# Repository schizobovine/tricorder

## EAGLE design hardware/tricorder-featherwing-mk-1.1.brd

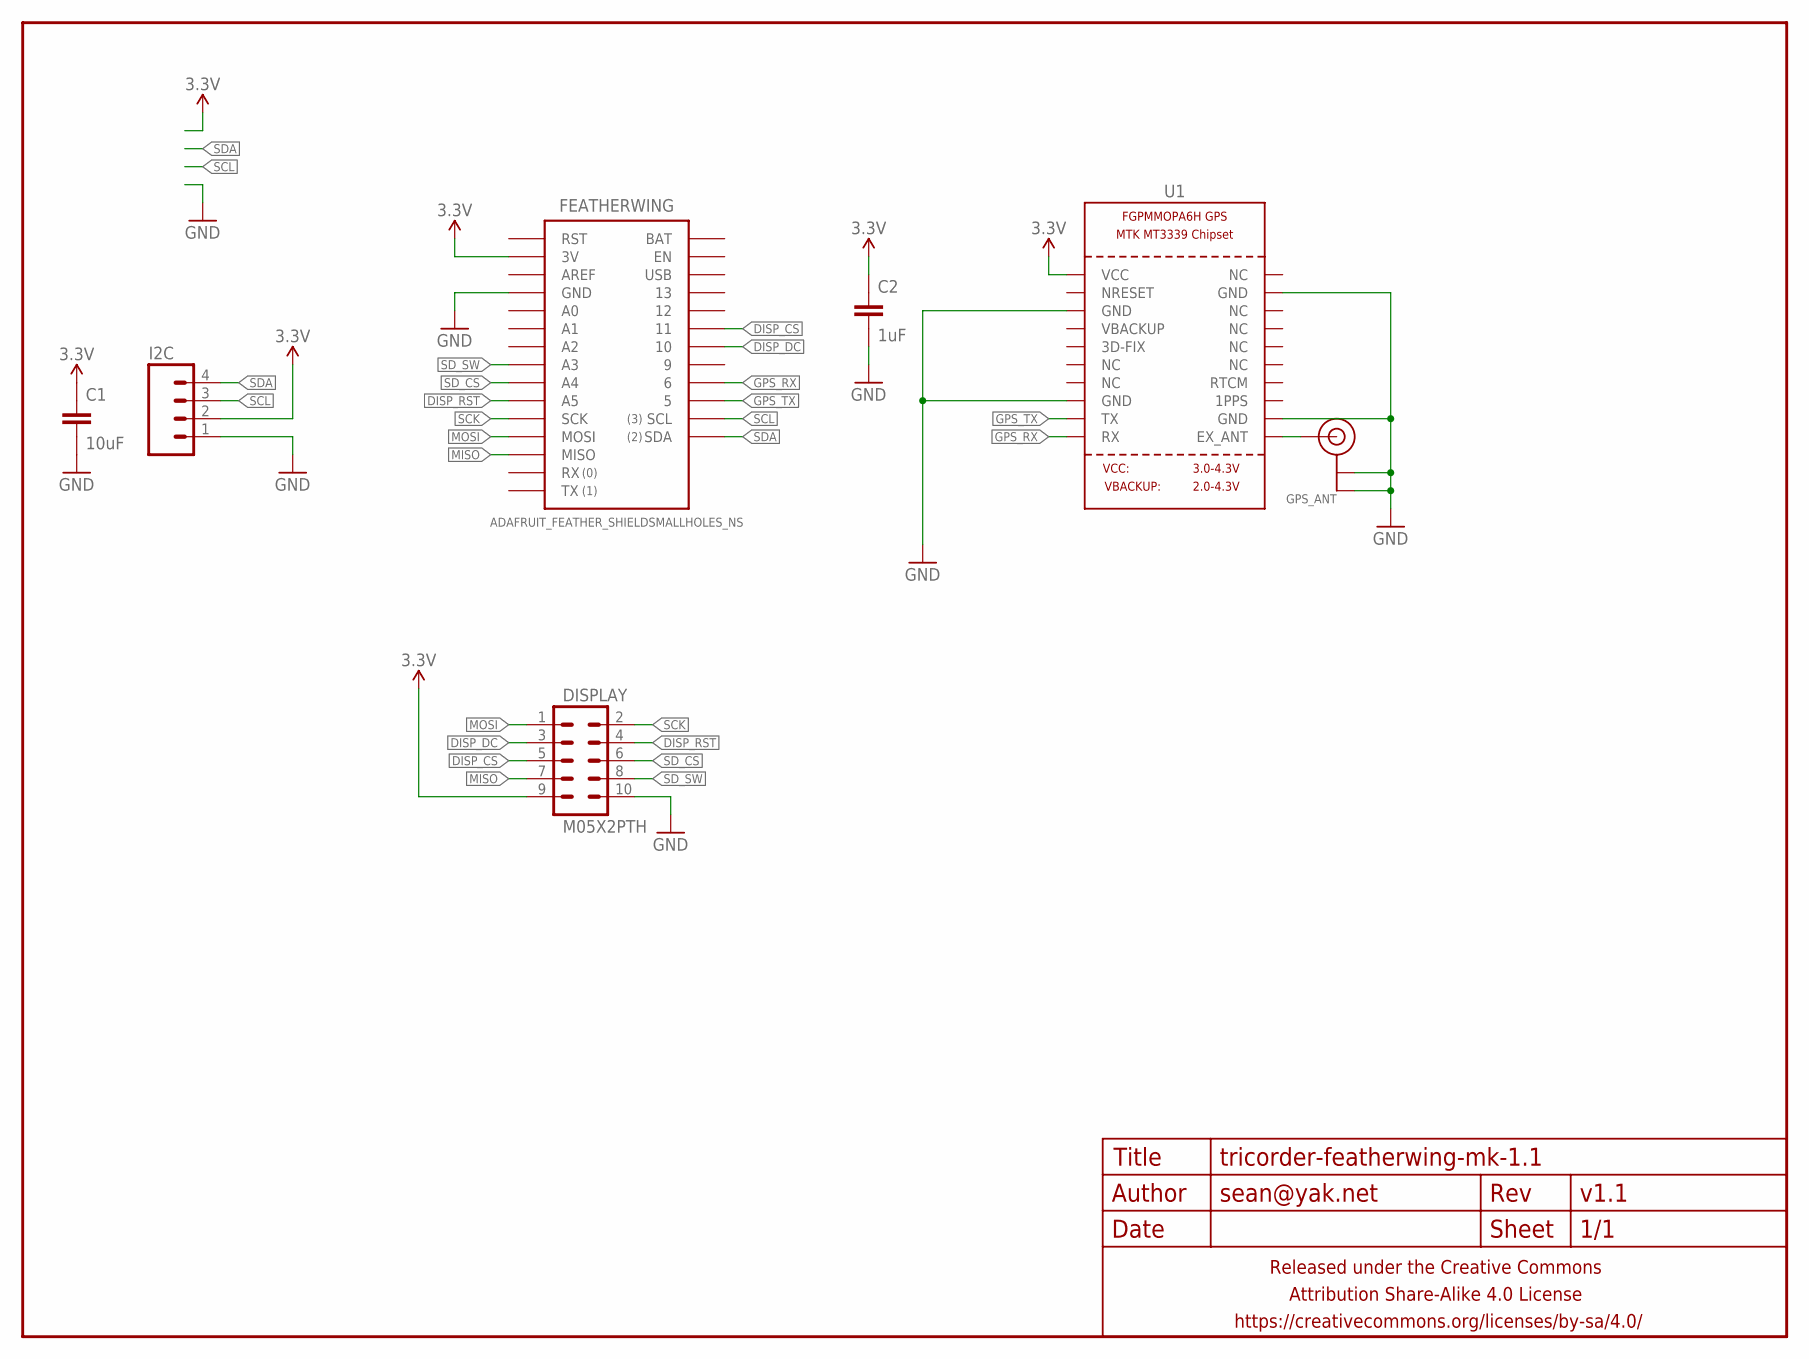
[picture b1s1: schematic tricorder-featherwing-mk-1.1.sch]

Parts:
C1: 10uF; C1210
C2: 1uF; C0603
DISPLAY: M05X2PTH; AVR_ICSP
FEATHERWING: ADAFRUIT_FEATHER_SHIELDSMALLHOLES_NS; ADAFRUIT_FEATHER_SMALLHOLES_NS
FRAME1: FRAME-LETTERNO_PACKAGE; DUMMY
GPS_ANT: ANTENNA_U.FL; U.FL
I2C: M04PTH; 1X04-PTH-VERT
U1: GPS_FGPMMOPA6H; FGPMMOPA6H

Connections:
3.3V: C1.1, C2.1, DISPLAY.9, FEATHERWING.3V, I2C.2, U1.P$1 (VCC)
DISP_CS: DISPLAY.5, FEATHERWING.11
DISP_DC: DISPLAY.3, FEATHERWING.10
DISP_RST: DISPLAY.4, FEATHERWING.A5
GND: C1.2, C2.2, DISPLAY.10, FEATHERWING.GND@0 (GND), FEATHERWING.GND@1 (GND), GPS_ANT.1 (GND), GPS_ANT.2 (GND), I2C.1, U1.P$3 (GND), U1.P$8 (GND), U1.P$12 (GND), U1.P$19 (GND)
GPS_RX: FEATHERWING.6, U1.P$10 (RX)
GPS_TX: FEATHERWING.5, U1.P$9 (TX)
MISO: DISPLAY.7, FEATHERWING.MISO
MOSI: DISPLAY.1, FEATHERWING.MOSI
unnamed: GPS_ANT.3 (SIGNAL), U1.P$11 (EX_ANT)
SCK: DISPLAY.2, FEATHERWING.SCK
SCL: FEATHERWING.SCL, I2C.3
SDA: FEATHERWING.SDA, I2C.4
SD_CS: DISPLAY.6, FEATHERWING.A4
SD_SW: DISPLAY.8, FEATHERWING.A3

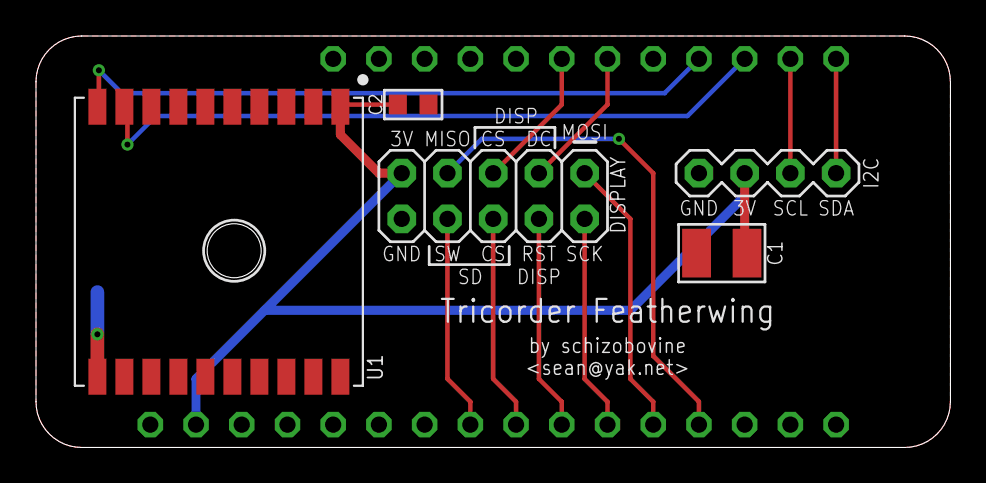
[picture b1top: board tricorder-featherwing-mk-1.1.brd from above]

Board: 2 copper layers, 50.8 x 22.9 mm, 8 parts (1 on the bottom side), 15 nets.

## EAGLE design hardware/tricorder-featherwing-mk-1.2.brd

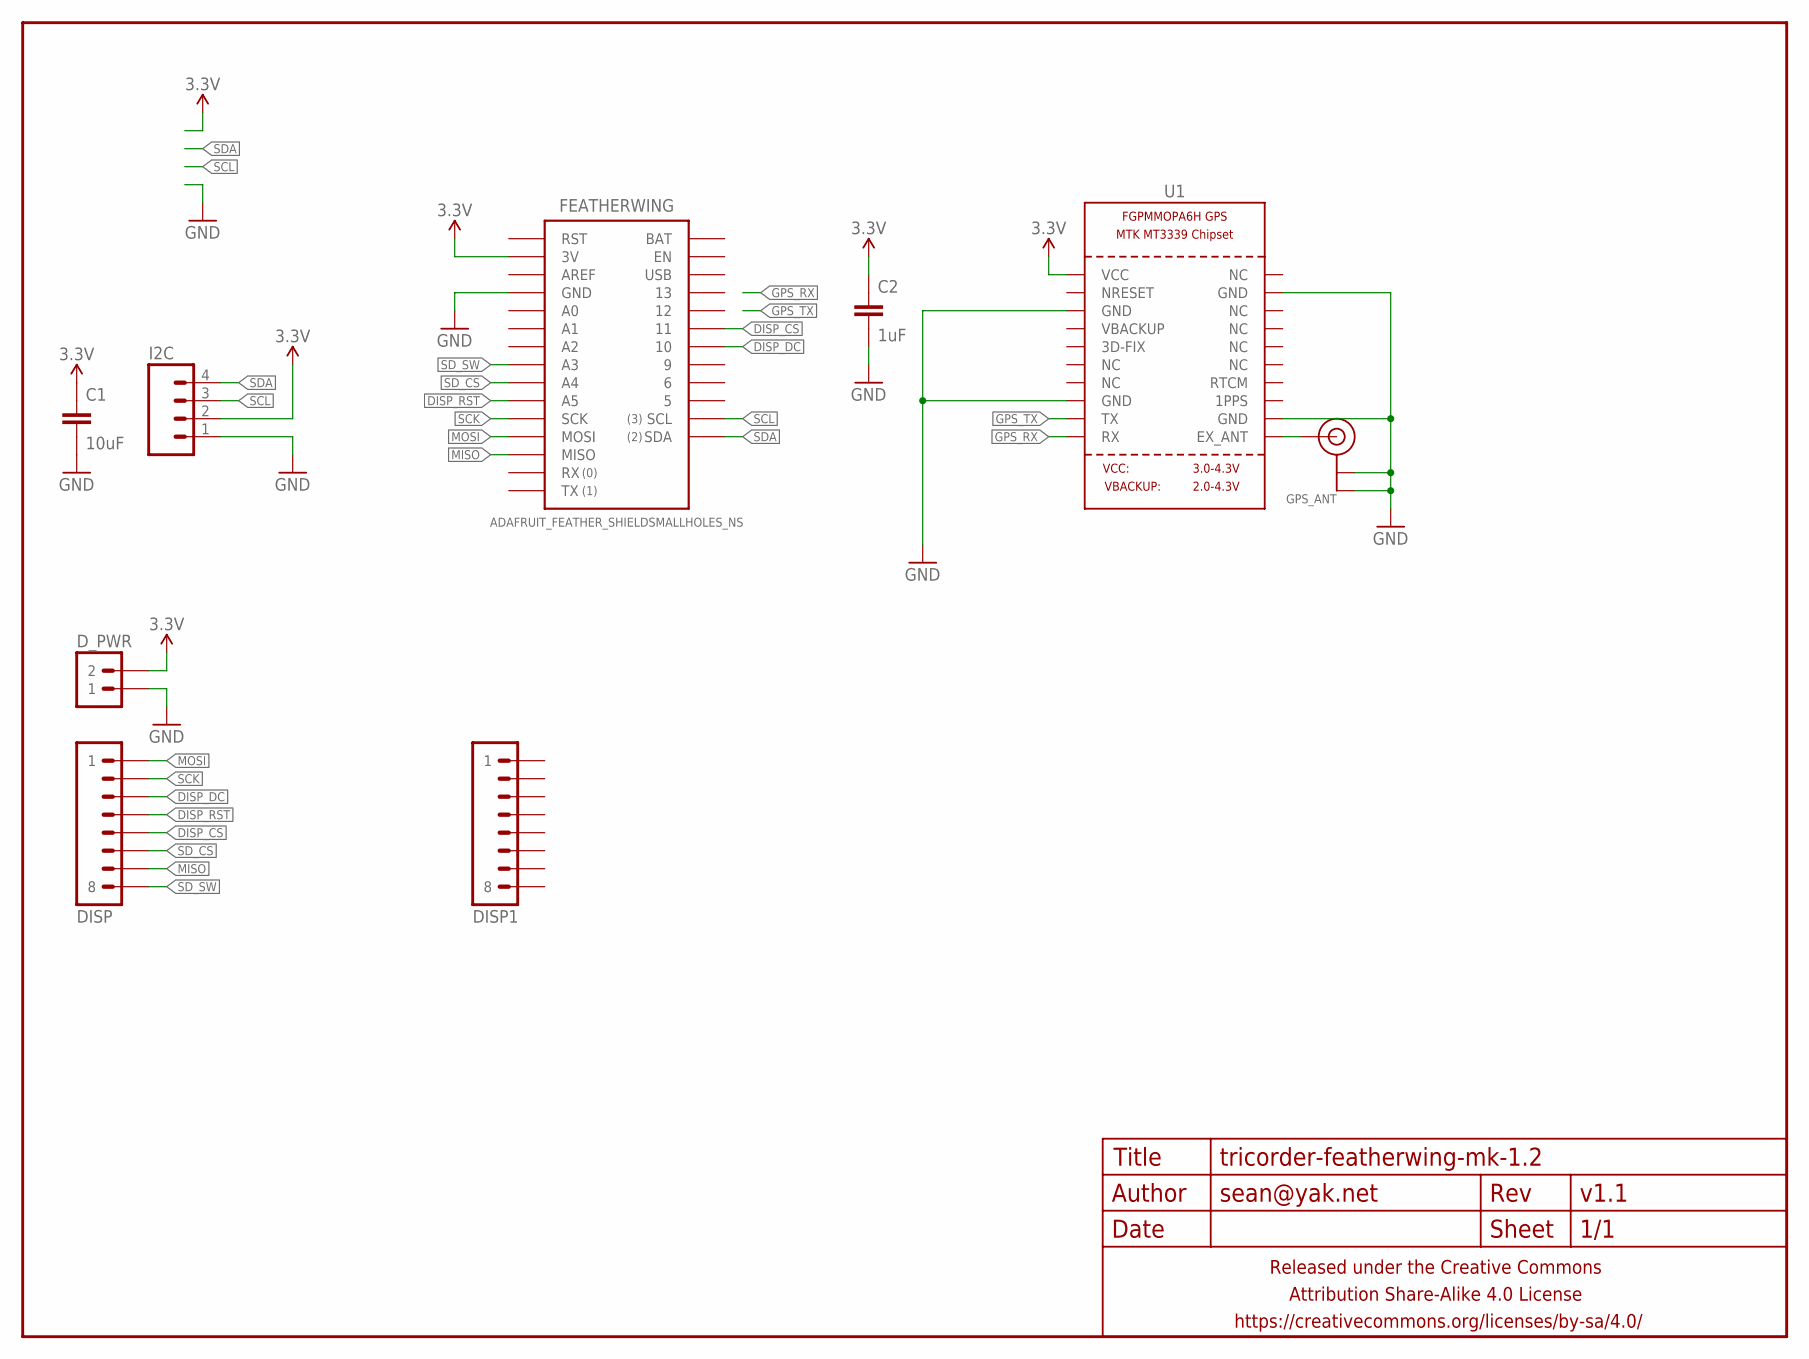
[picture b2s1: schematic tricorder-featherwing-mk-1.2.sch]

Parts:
C1: 10uF; C1210
C2: 1uF; C0603
DISP, DISP1: M081X08; 1X08
D_PWR: M02PTH; 1X02
FEATHERWING: ADAFRUIT_FEATHER_SHIELDSMALLHOLES_NS; ADAFRUIT_FEATHER_SMALLHOLES_NS
FRAME1: FRAME-LETTERNO_PACKAGE; DUMMY
GPS_ANT: ANTENNA_U.FL; U.FL
I2C: M04PTH; 1X04-PTH-VERT
U1: GPS_FGPMMOPA6H; FGPMMOPA6H

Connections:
3.3V: C1.1, C2.1, D_PWR.2, FEATHERWING.3V, I2C.2, U1.P$1 (VCC)
DISP_CS: DISP.5, FEATHERWING.11
DISP_DC: DISP.3, FEATHERWING.10
DISP_RST: DISP.4, FEATHERWING.A5
GND: C1.2, C2.2, D_PWR.1, FEATHERWING.GND@0 (GND), FEATHERWING.GND@1 (GND), GPS_ANT.1 (GND), GPS_ANT.2 (GND), I2C.1, U1.P$3 (GND), U1.P$8 (GND), U1.P$12 (GND), U1.P$19 (GND)
GPS_RX: U1.P$10 (RX)
GPS_TX: U1.P$9 (TX)
MISO: DISP.7, FEATHERWING.MISO
MOSI: DISP.1, FEATHERWING.MOSI
unnamed: GPS_ANT.3 (SIGNAL), U1.P$11 (EX_ANT)
SCK: DISP.2, FEATHERWING.SCK
SCL: FEATHERWING.SCL, I2C.3
SDA: FEATHERWING.SDA, I2C.4
SD_CS: DISP.6, FEATHERWING.A4
SD_SW: DISP.8, FEATHERWING.A3

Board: 2 copper layers, 10 parts (1 on the bottom side), 13 nets, no tracks yet.

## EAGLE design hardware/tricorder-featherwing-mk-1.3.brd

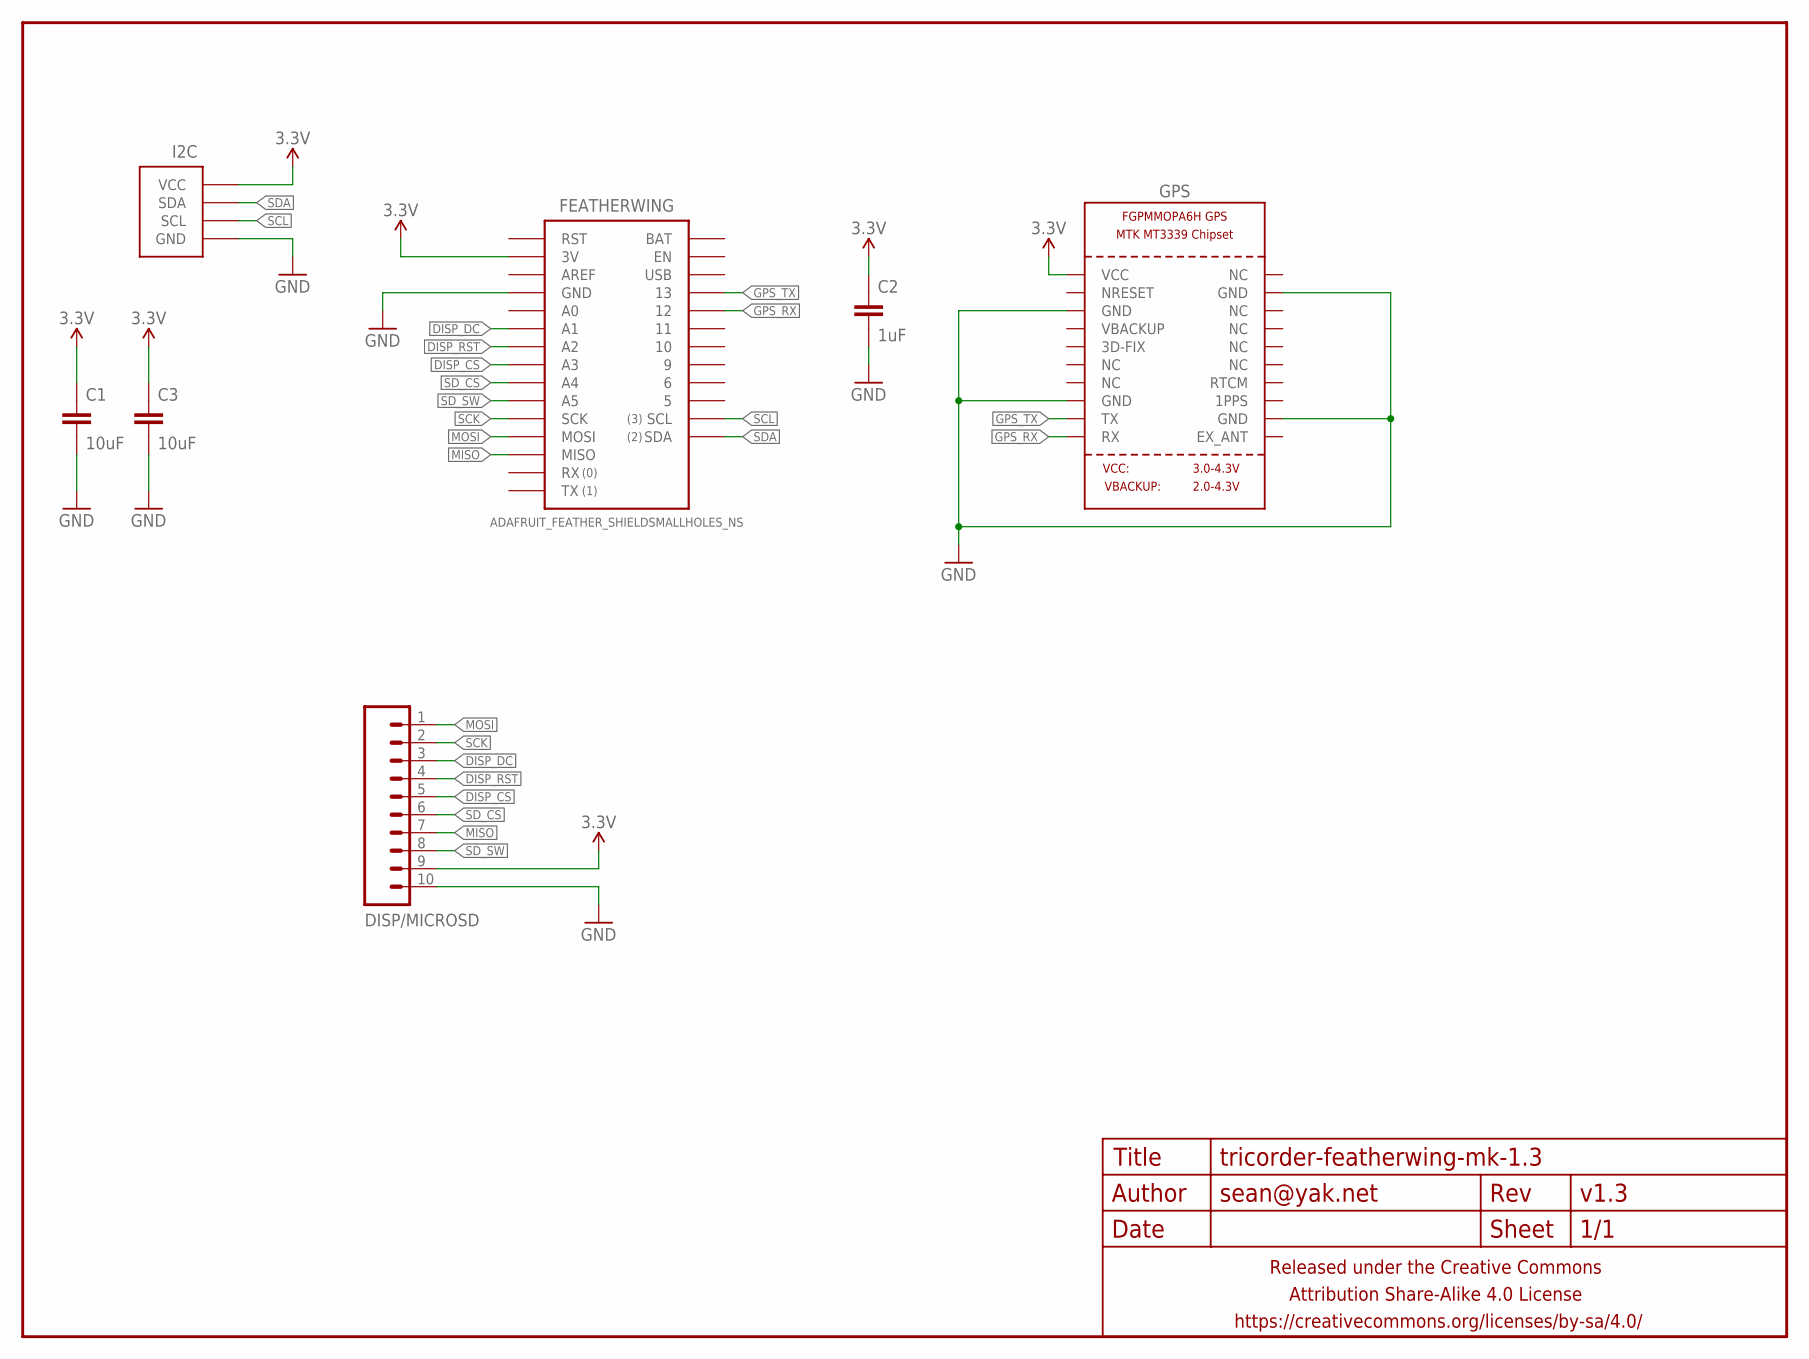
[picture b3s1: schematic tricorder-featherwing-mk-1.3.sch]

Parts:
C1, C3: 10uF; C1210
C2: 1uF; C0603
DISP/MICROSD: M10JST-10-PH-RA-PTH; JST-10-PH-RA-PTH
FEATHERWING: ADAFRUIT_FEATHER_SHIELDSMALLHOLES_NS; ADAFRUIT_FEATHER_SMALLHOLES_NS
FRAME1: FRAME-LETTERNO_PACKAGE; DUMMY
GPS: GPS_FGPMMOPA6H; FGPMMOPA6H
I2C: M04-I2CPTH-0.1IN-CENTERED; 1X04-PTH-VERT-I2C-CENTERED

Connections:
3.3V: C1.1, C2.1, C3.1, DISP/MICROSD.9, FEATHERWING.3V, GPS.P$1 (VCC), I2C.VCC
DISP_CS: DISP/MICROSD.5, FEATHERWING.A3
DISP_DC: DISP/MICROSD.3, FEATHERWING.A1
DISP_RST: DISP/MICROSD.4, FEATHERWING.A2
GND: C1.2, C2.2, C3.2, DISP/MICROSD.10, FEATHERWING.GND@0 (GND), FEATHERWING.GND@1 (GND), GPS.P$3 (GND), GPS.P$8 (GND), GPS.P$12 (GND), GPS.P$19 (GND), I2C.GND
GPS_RX: FEATHERWING.12, GPS.P$10 (RX)
GPS_TX: FEATHERWING.13, GPS.P$9 (TX)
MISO: DISP/MICROSD.7, FEATHERWING.MISO
MOSI: DISP/MICROSD.1, FEATHERWING.MOSI
SCK: DISP/MICROSD.2, FEATHERWING.SCK
SCL: FEATHERWING.SCL, I2C.SCL
SDA: FEATHERWING.SDA, I2C.SDA
SD_CS: DISP/MICROSD.6, FEATHERWING.A4
SD_SW: DISP/MICROSD.8, FEATHERWING.A5

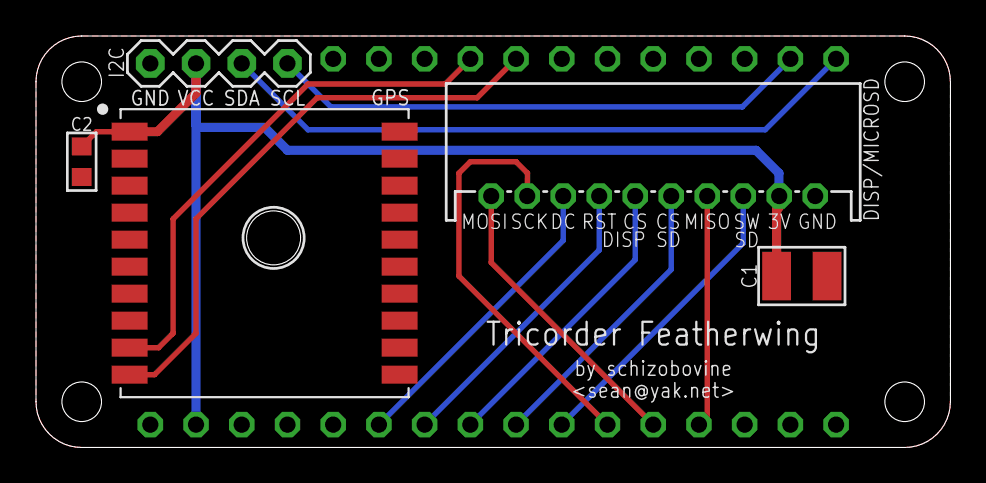
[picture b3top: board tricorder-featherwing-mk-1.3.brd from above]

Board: 2 copper layers, 50.8 x 22.9 mm, 8 parts (1 on the bottom side), 14 nets.

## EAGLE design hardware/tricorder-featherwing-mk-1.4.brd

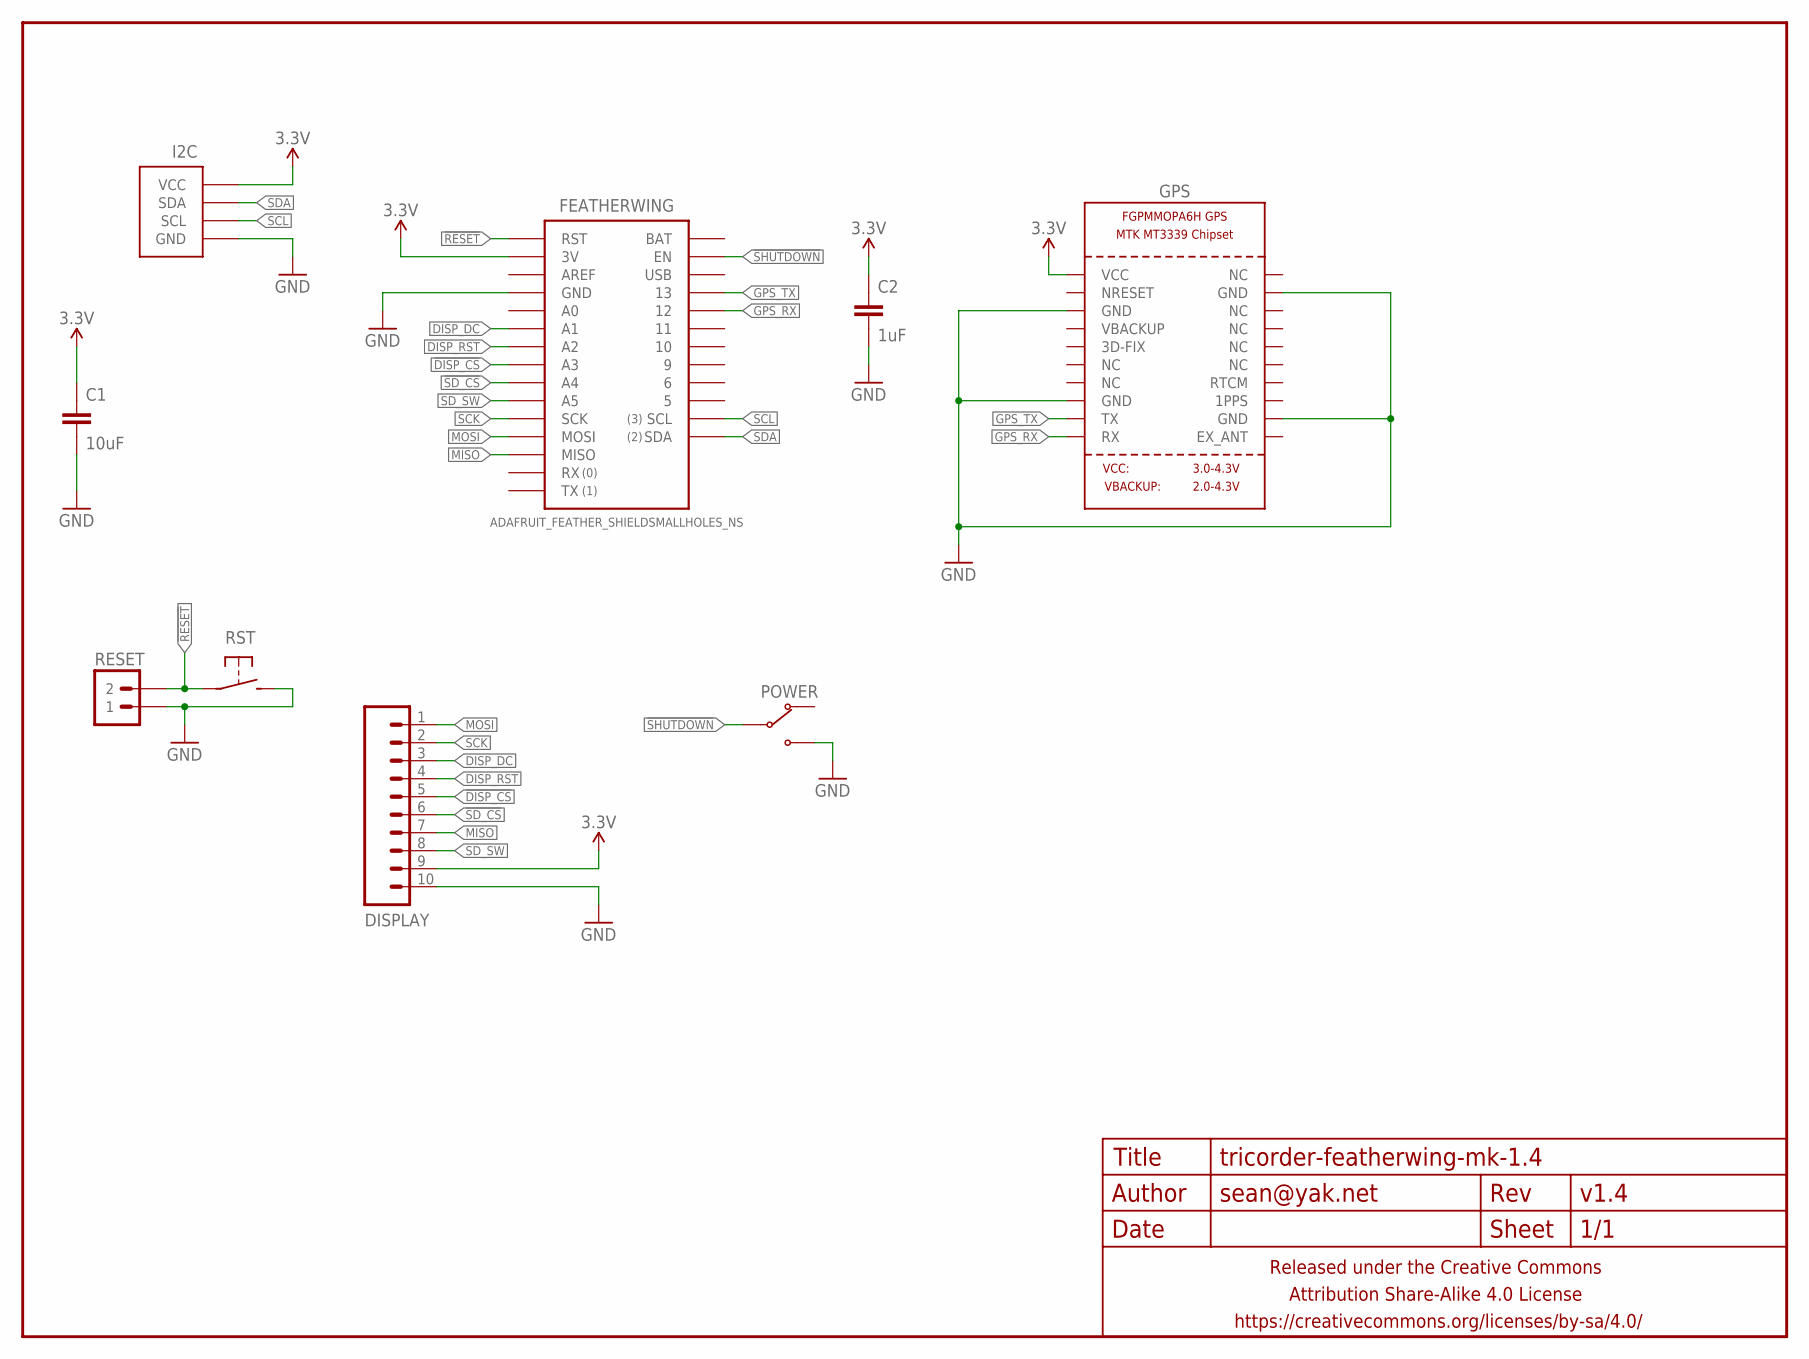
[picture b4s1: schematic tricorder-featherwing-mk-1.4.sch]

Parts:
C1: 10uF; C1210
C2: 1uF; C0603
DISPLAY: M10JST-10-PH-RA-PTH; JST-10-PH-RA-PTH
FEATHERWING: ADAFRUIT_FEATHER_SHIELDSMALLHOLES_NS; ADAFRUIT_FEATHER_SMALLHOLES_NS
FRAME1: FRAME-LETTERNO_PACKAGE; DUMMY
GPS: GPS_FGPMMOPA6H; FGPMMOPA6H
I2C: M04-I2CJST-4-PH-RA-CENTERED; 1X04-JST-PH-RA-PTH-I2C-CENTERED
POWER: SWITCH-SPDTSMD-RA; SWITCH-SPDT-SMD-RA
RESET: M02PTH-CENTERED; 1X02-CENTER
RST: SPST-NO-TACT3MM-PTH-SMALL-PADS; DTS-3-SMALL-PADS

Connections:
3.3V: C1.1, C2.1, DISPLAY.9, FEATHERWING.3V, GPS.P$1 (VCC), I2C.2 (VCC)
!DISP_CS: DISPLAY.5, FEATHERWING.A3
!RESET: FEATHERWING.RST, RESET.2, RST.1
!SD_CS: DISPLAY.6, FEATHERWING.A4
!SHUTDOWN: FEATHERWING.EN, POWER.2 (COM)
DISP_DC: DISPLAY.3, FEATHERWING.A1
DISP_RST: DISPLAY.4, FEATHERWING.A2
GND: C1.2, C2.2, DISPLAY.10, FEATHERWING.GND@0 (GND), FEATHERWING.GND@1 (GND), GPS.P$3 (GND), GPS.P$8 (GND), GPS.P$12 (GND), GPS.P$19 (GND), I2C.1 (GND), POWER.1 (NO), RESET.1, RST.2
GPS_RX: FEATHERWING.12, GPS.P$10 (RX)
GPS_TX: FEATHERWING.13, GPS.P$9 (TX)
MISO: DISPLAY.7, FEATHERWING.MISO
MOSI: DISPLAY.1, FEATHERWING.MOSI
SCK: DISPLAY.2, FEATHERWING.SCK
SCL: FEATHERWING.SCL, I2C.4 (SCL)
SDA: FEATHERWING.SDA, I2C.3 (SDA)
SD_SW: DISPLAY.8, FEATHERWING.A5

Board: 2 copper layers, 10 parts (1 on the bottom side), 16 nets, no tracks yet.

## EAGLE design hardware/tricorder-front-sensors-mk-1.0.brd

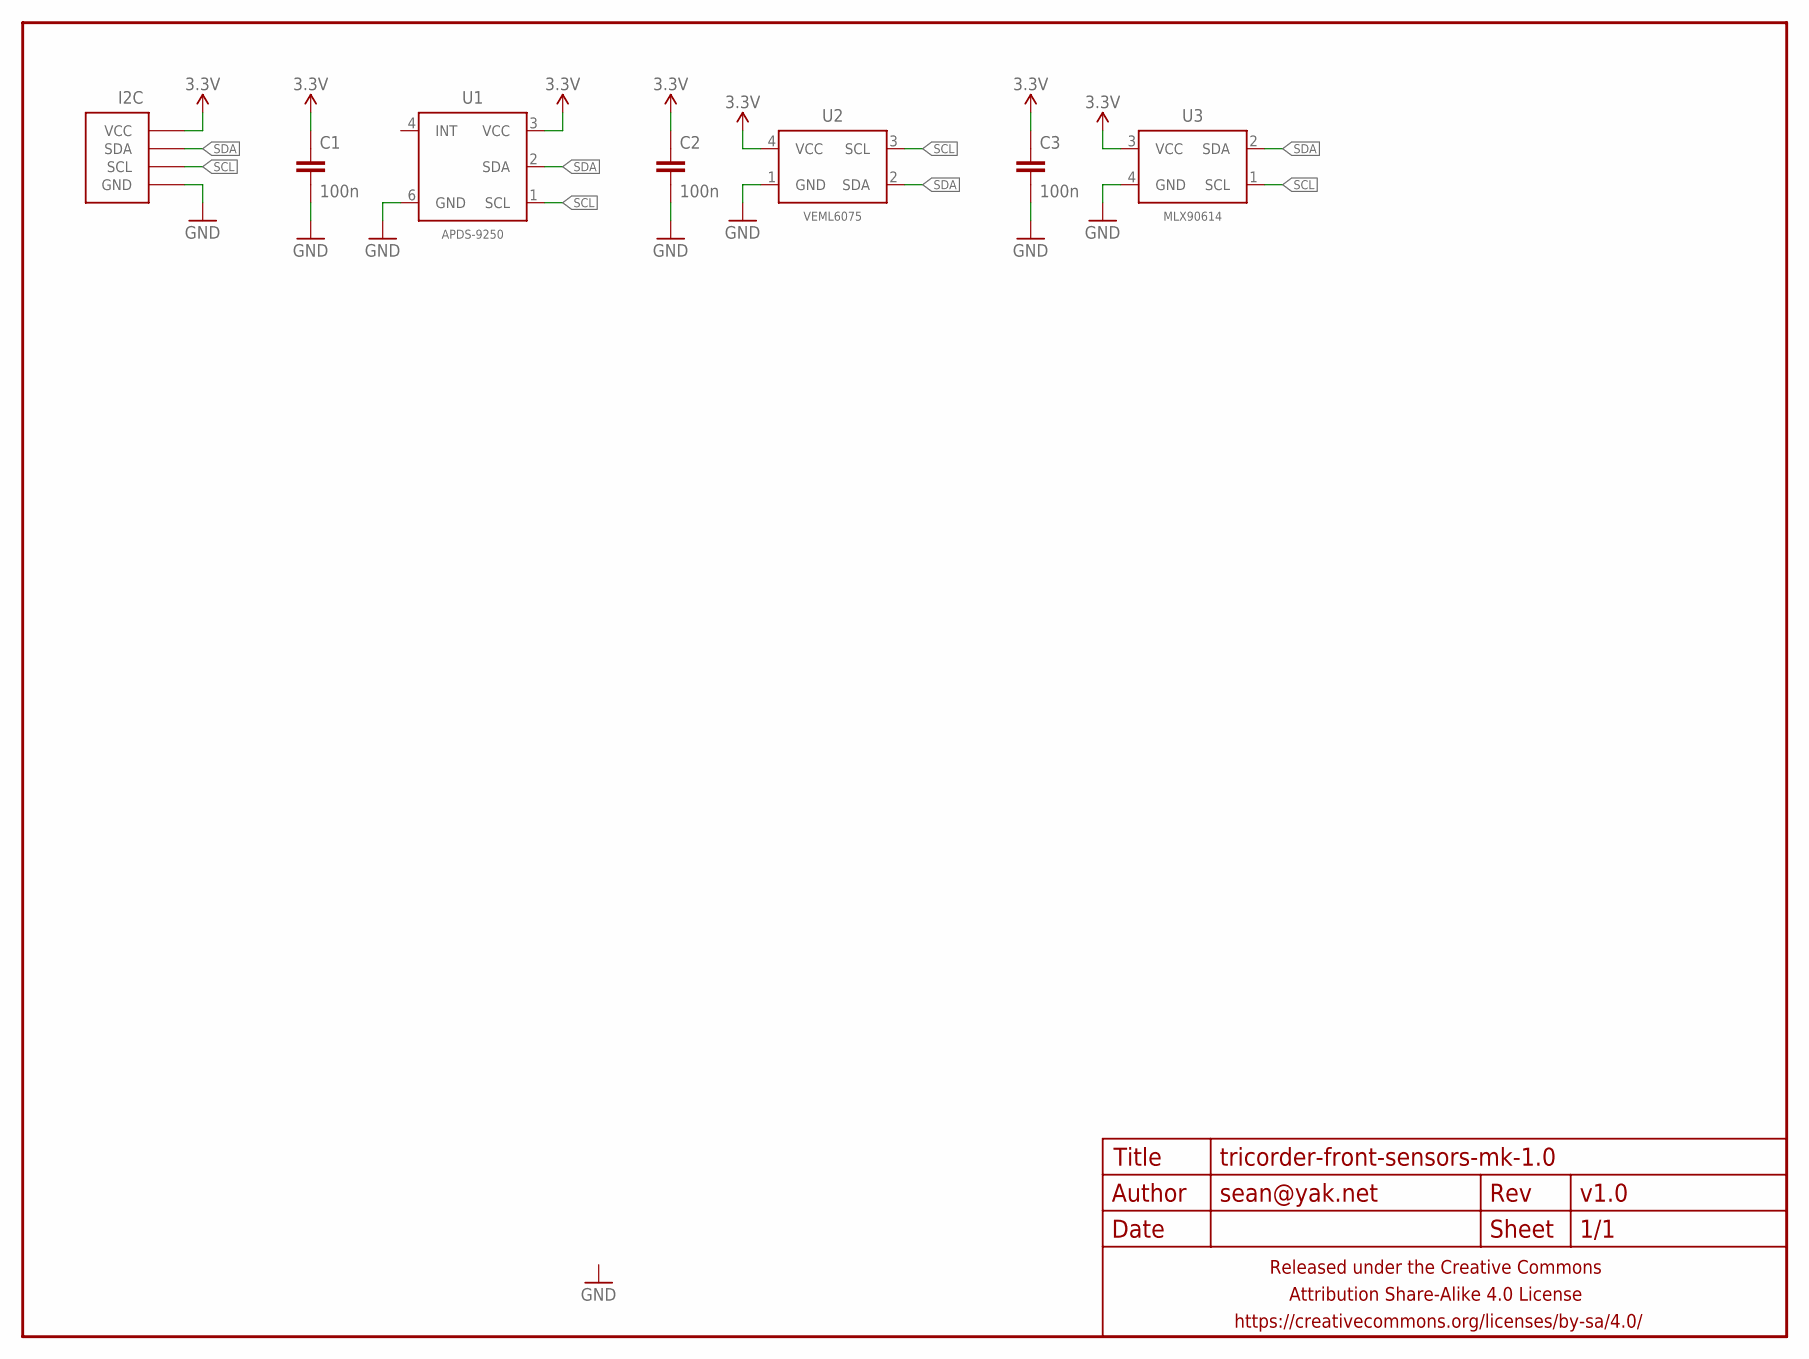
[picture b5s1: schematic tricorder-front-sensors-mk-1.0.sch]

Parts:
C1, C2, C3: 100n; C0603
FRAME1: FRAME-LETTERNO_PACKAGE; DUMMY
I2C: M04-I2CJST-4-PH-VERT-CENTERED-I2C; JST-4-PH-VERT-PTH-CENTERED-I2C
U1: APDS-9250
U2: VEML6075; OPLGA4
U3: MLX90614; TO-39-4

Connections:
3.3V: C1.1, C2.1, C3.1, I2C.2 (VCC), U1.3 (VCC), U2.4 (VCC), U3.3 (VCC)
GND: C1.2, C2.2, C3.2, I2C.1 (GND), U1.6 (GND), U2.1 (GND), U3.4 (GND)
SCL: I2C.4 (SCL), U1.1 (SCL), U2.3 (SCL), U3.1 (SCL)
SDA: I2C.3 (SDA), U1.2 (SDA), U2.2 (SDA), U3.2 (SDA)

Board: 2 copper layers, 8 parts (2 on the bottom side), 4 nets, no tracks yet.

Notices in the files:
parts and their libraries:
a_parts: Released under the Creative Commons Attribution Share-Alike 4.0 License
a_parts: https://creativecommons.org/licenses/by-sa/4.0
a_parts: Released under the Creative Commons
